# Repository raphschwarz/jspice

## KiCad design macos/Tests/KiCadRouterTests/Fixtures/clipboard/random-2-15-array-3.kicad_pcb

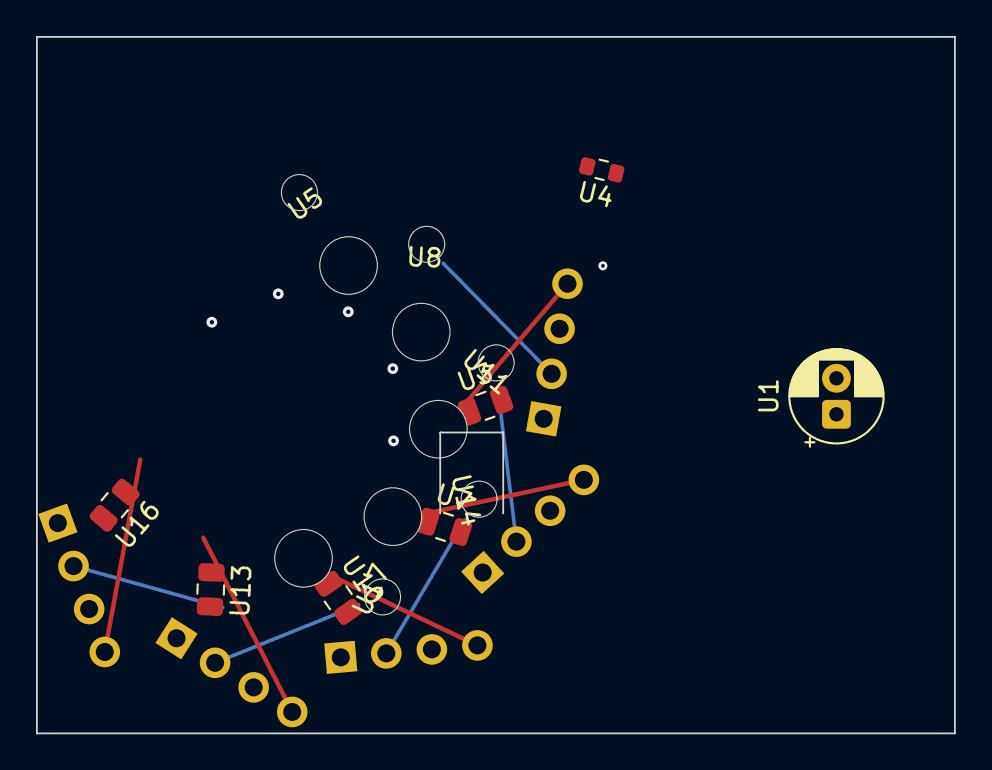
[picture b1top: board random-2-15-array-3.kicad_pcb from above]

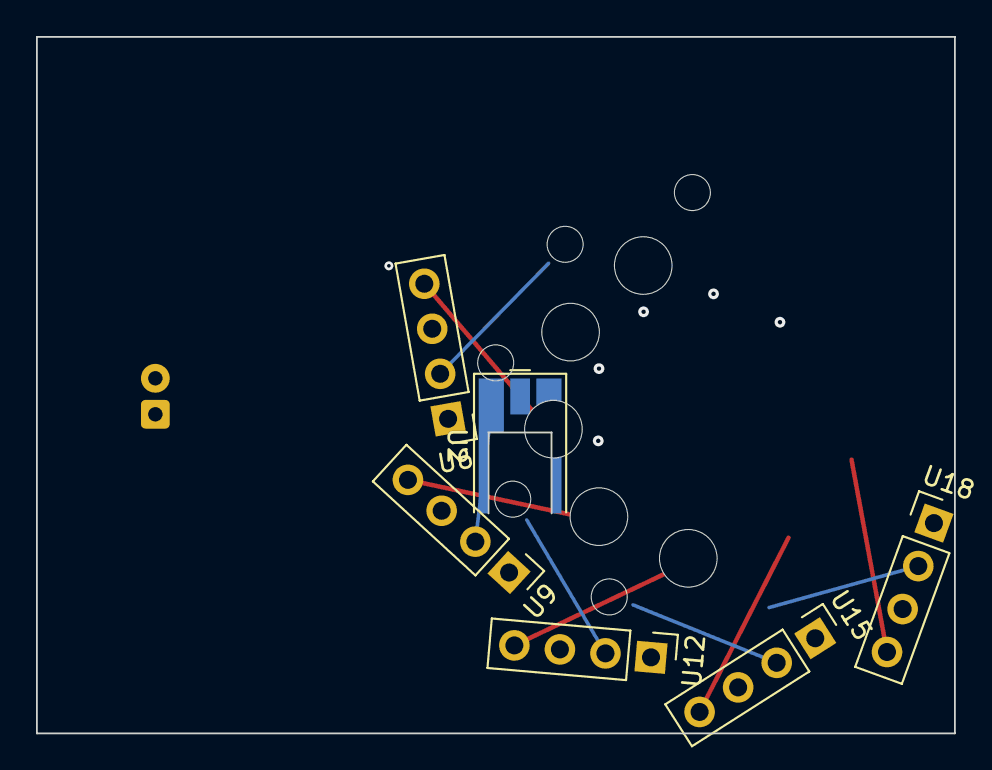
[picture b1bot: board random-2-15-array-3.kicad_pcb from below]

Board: 2 copper layers, 51.0 x 38.7 mm, 18 parts (6 on the bottom side), 2 nets.

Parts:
U1: CP_Radial_D5.0mm_P2.00mm
U2: MMCX_Molex_73415-0961_Horizontal_0.8mm-PCB
U3, U7, U10, U13, U16: C_0805_2012Metric
U4: R_0603_1608Metric
U5, U8, U11, U14, U17: MountingHole_3.2mm_M3
U6, U9, U12, U15, U18: PinHeader_1x04_P2.54mm_Vertical

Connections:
N3: U1.1, U3.1, U6.1, U6.2, U7.1, U9.1, U9.2, U10.1, U12.1, U12.2, U13.1, U15.1, U15.2, U16.1, U18.1, U18.2
PWR_5V: U6.3, U9.3, U12.3, U15.3, U18.3
